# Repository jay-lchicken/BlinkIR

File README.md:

## To the previous review
"Hey! Cool project, but it needs to be polished a bit before it can be approved, you can organise the files in speicific folders such as PCB/etc. I also believe this can be cost optimized a lot, please take a look at the docs, right now you can get 54$ worth of grant for the project but your BOM is totalling to 3 times of that, you should save costs on the PCBA, by trying to fit all components on one side, using components only from standard libray, getting only 2 pcba rather than 5, etc."

I will reorganise the files into the folders. However, for the cost optimisation, it is not really possible for this project since the LEDs cannot be on the same side as the phototransistor and thus require a double-sided assembly. Getting only 2pcba rather than 5 only saves $10, so I may as well go with 5. I can pay the extra price that the grant cannot cover. also, some components are really big and cannot be on the same side as phototransistor else it would hit the ground, like the 47uf electrolytic capacitor

### The sample code in the repository basically lights up the corresponding LEDs when the phototransistor detects black. The code also uses button 1 to start the program
# Introduction

I created this project when I saw a super fast line tracing robot. I thought about what was needed and since one of the most crucial components for a line tracing robot is the IR Array Sensor, I decided

What if I can make one of the most responsive and feature-packed IR Sensor ever made.

# Description

I took inspiration from the Pololu QTR-8A. It is equipped with 8 IR emitters and 8 IR Recievers (or maybe phototransistors, I'm not sure).

I did the same and put it into my PCB with 8 IR emitters and 8 phototransistors that uses the voltage divider rule to give users the reading.

Doing this, I realised that the project ended up being just a normal IR Array sensor. I thought hard about how I could make it unique. Personally, I have building robots since young and it came to my mind
that if I can solve all the problems I previously had with a robot by implementing the solution in the PCB, it would be great! 

I usually hate using the Serial Monitor when debugging my hardware code, so I decided to add 8 SK6812 Neopixel indicator lights to the pcb, one for each IR Sensor but on the other side of the PCB.
The user can have full control of the LEDs but for me, I want to be able to change the light depending on what the phototransistor detects. This helps make debugging with the IR array sensor a lot easier.
When testing line tracking, I can also easily see how I can fine tune the robot when line tracking by looking at the LEDs which I can program to light up when it detects a certain black that meets the treshold value

Competitive robots require a Start/Stop button which I normally use jumper wires to implement. However, these wires often get loose and prevent the robot from starting. Since I am already desiging a PCB, I might as well put some buttons

# How it all fits together
I added a Buck-Boost converter which allow you to put 3.3V to 12V into the IR array sensor. Then, the converter will convert it to 5V which is the proper operating voltage for the circuit.
There are 8 pins which the users can tap into individually with their microcontroller to read the phototransistor readings. There are also another 3 pins. Two for the two INPUT_PULLUP Buttons as well as one for contorlling the daisy chained SK6812 Neopixel LEDs.
Lastly, there are another 3 pins for Vin, GND and turning on the IR Emitter

I decided to go with 4.7K resistors for the phototransistors, this helps balance between the noise and speed for the IR Array Sensor
# Some Schematic Images

# BOM 

## 🧾 Components

| Part Number | Selected By | Qty | Cost |
|------------|------------|-----|------|
| FRC1206F4700TS | System | 15 | $0.08 |
| 0402WGF3300TCE | System | 20 | $0.02 |
| CL10A106KP8NNNC | System | 40 | $0.36 |
| 0603WAF1003T5E | System | 40 | $0.03 |
| NTD3528I7 | System | 44 | $1.66 |
| TPS63070RNMT | System | 5 | $8.42 |
| CL31A226KAHNNNE | System | 14 | $2.50 |
| 0805W8F4702T5E | System | 20 | $0.04 |
| 0805W8F5233T5E | System | 20 | $0.05 |
| KT-0603W | System | 20 | $0.24 |
| RVT102470M0505 | Customer | 20 | $0.58 |
| SK6812 | System | 42 | $3.73 |
| 0805W8F4701T5E | System | 46 | $0.10 |
| 2.54-1×3P# | Customer | 12 | $0.29 |
| MPT0603GT | System | 44 | $1.83 |
| CL05B104K05NNNC | System | 40 | $0.05 |
| 1206W4F1002T5E | System | 15 | $0.09 |
| CMI060808U22RK7 | System | 20 | $0.34 |
| JSM2302 | Customer | 15 | $0.30 |
| CL10A105KB8NNNC | System | 20 | $0.22 |
| KMR221GLFS | System | 10 | $5.31 |
| 0603WAF470J5E | System | 40 | $0.08 |

## 💰 Cost Summary

| Category | Amount |
|----------|--------|
| Merchandise Total (incl. assembly) | $153.07 |
| Shipping (Estimated) | $8.85 |
| **Subtotal** | **$161.92** |

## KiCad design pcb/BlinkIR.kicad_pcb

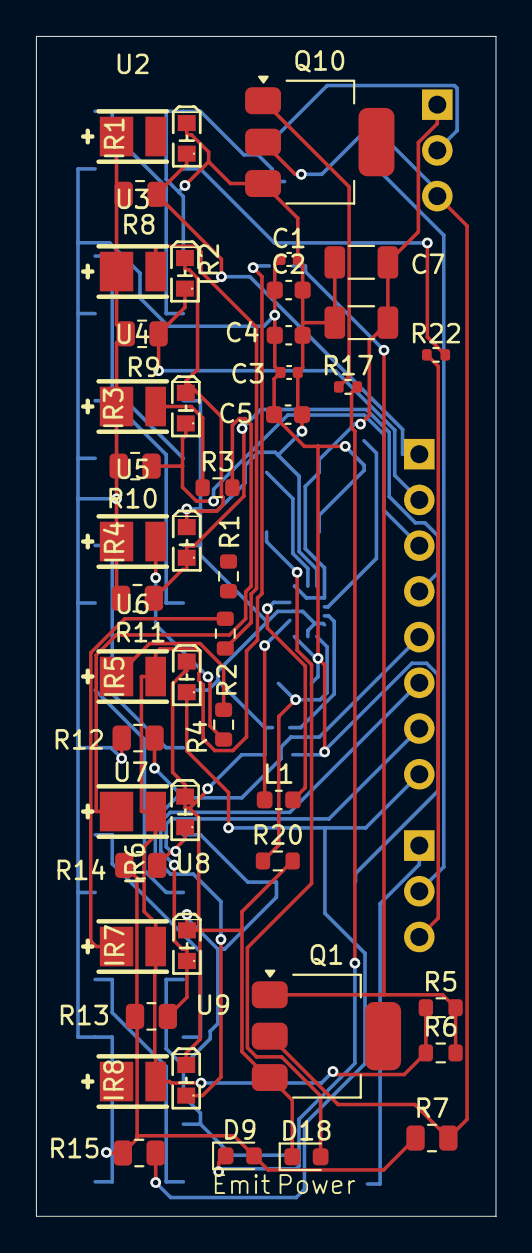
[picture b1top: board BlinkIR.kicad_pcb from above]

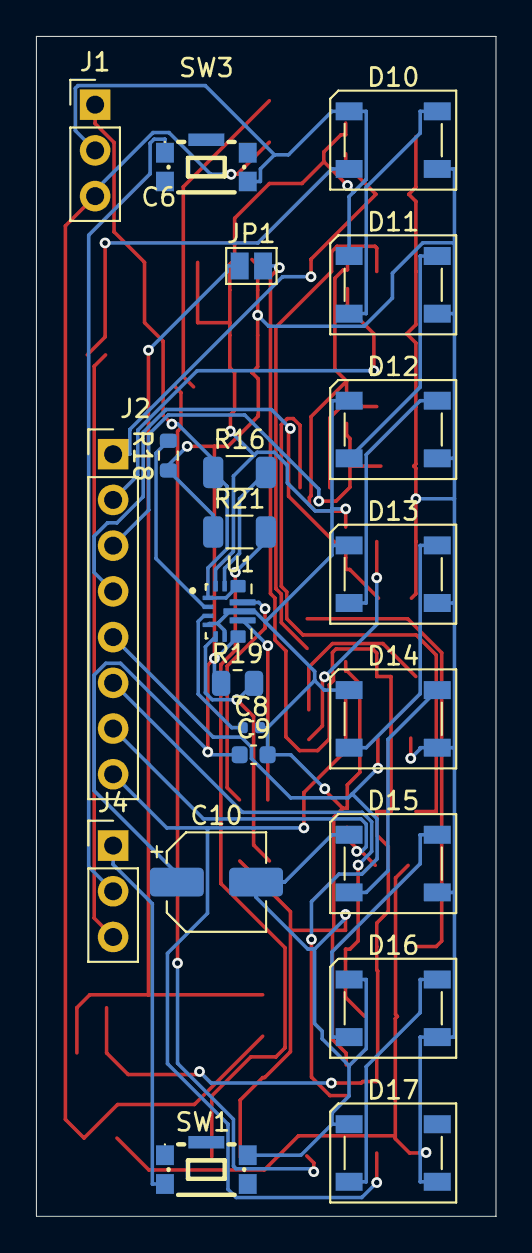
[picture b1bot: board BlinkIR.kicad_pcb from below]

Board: 2 copper layers, 25.5 x 65.6 mm, 68 parts (22 on the bottom side), 42 nets.

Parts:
C1, C3: 0.1uF; C_0402_1005Metric
C2, C4: 1.0uF; C_0603_1608Metric
C5, C9: 10uF; C_0603_1608Metric
C6, C7: 22uF; C_1206_3216Metric
C8: 100nF; C_0402_1005Metric
C10: 47uF; CP_Elec_5x5.4
D9, D18: LED; LED_0603_1608Metric
D10, D11, D12, D13, D14, D15, D16, D17: SK6812; LED_SK6812_PLCC4_5.0x5.0mm_P3.2mm
IR1, IR2, IR3, IR4, IR5, IR6, IR7, IR8: MPT60363T; OPTO-SMD_L1.7-W0.8
J1, J4: Conn_01x03_Pin; PinHeader_1x03_P2.54mm_Vertical
J2: Conn_01x08_Pin; PinHeader_1x08_P2.54mm_Vertical
JP1: SolderJumper_2_Open; SolderJumper-2_P1.3mm_Open_Pad1.0x1.5mm
L1: 2.2uH; L_0603_1608Metric
Q1, Q10: NMOS; SOT-223
R1, R2, R3, R4, R5, R6: 47; R_0603_1608Metric
R7: 47k; R_0805_2012Metric
R8, R9, R10, R11, R12, R13, R14, R15: 4.7k; R_0805_2012Metric
R16: 10k; R_1206_3216Metric
R17, R22: 330; R_0402_1005Metric
R18, R20: 100k; R_0603_1608Metric
R19: 523k; R_0805_2012Metric
R21: 470; R_1206_3216Metric
SW1, SW3: KMR221GLFS; KEY-SMD_KMR2XXGXXX
U1: TPS63070RNMT; VREG_TPS63070RNMT
U2, U3, U4, U5, U6, U7, U8, U9: NTD3528I7; LED-SMD_L3.5-W2.8-FD-1

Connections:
/IR1: IR1.1 (C), J2.1, R8.2
/IR2: IR2.1 (C), J2.2, R9.2
/IR3: IR3.1 (C), J2.3, R10.2
/IR4: IR4.1 (C), J2.4, R11.2
/IR5: IR8.1 (C), J2.5, R12.2
/IR6: IR7.1 (C), J2.6, R13.2
/IR7: IR6.1 (C), J2.7, R14.2
/IR8: IR5.1 (C), J2.8, R15.2
/IR_ON: J1.3, Q1.2 (G), Q10.2 (G), R7.2
GND: C1.2, C2.2, C3.2, C4.2, C5.2, C6.1, C7.1, C8.2, C9.2, C10.2, D10.1 (VSS), D11.1 (VSS), D12.1 (VSS), D13.1 (VSS), D14.1 (VSS), D15.1 (VSS), D16.1 (VSS), D17.1 (VSS), D18.1 (K), IR1.2 (E), IR2.2 (E), IR3.2 (E), IR4.2 (E), IR5.2 (E), IR6.2 (E), IR7.2 (E), IR8.2 (E), J1.2, Q1.3 (S), Q10.3 (S), R20.2, SW1.2, SW3.4, U1.4 (GND), U1.6 (FB2), U1.10 (PGND), U1.15 (VSEL)
unnamed: D9.1 (K), R17.2
unnamed: D10.2 (DIN), R22.2
unnamed: D10.4 (DOUT), D11.2 (DIN)
unnamed: D11.4 (DOUT), D12.2 (DIN)
unnamed: D12.4 (DOUT), D13.2 (DIN)
unnamed: D13.4 (DOUT), D14.2 (DIN)
unnamed: D14.4 (DOUT), D15.2 (DIN)
unnamed: D15.4 (DOUT), D16.2 (DIN)
unnamed: D16.4 (DOUT), D17.2 (DIN)
unnamed: D18.2 (A), R21.2
unnamed: J4.1, SW1.3
unnamed: J4.2, SW3.1
unnamed: J4.3, R22.1
unnamed: JP1.1 (A), Q1.1 (D), R5.2, R6.2
unnamed: JP1.2 (B), R5.1, R6.1, U6.2, U7.2, U8.2, U9.2
unnamed: Q10.1 (D), R17.1
unnamed: R1.1, U2.2
unnamed: R1.2, U9.1
unnamed: R2.1, U3.2
unnamed: R2.2, U8.1
unnamed: R3.1, U4.2
unnamed: R3.2, U7.1
unnamed: R4.1, U5.2
unnamed: R4.2, U6.1
unnamed: R16.2, U1.14 (EN)
unnamed: R19.2, R20.1, U1.5 (FB)
unnamed: L1.2, U1.11 (L1)
unnamed: L1.1, U1.9 (L2)
unnamed: R18.2, U1.2 (PG)
unnamed: C8.1, U1.3 (VAUX)
VCC: C1.1, C2.1, C3.1, C4.1, C5.1, C9.1, C10.1, D9.2 (A), D10.3 (VDD), D11.3 (VDD), D12.3 (VDD), D13.3 (VDD), D14.3 (VDD), D15.3 (VDD), D16.3 (VDD), D17.3 (VDD), R7.1, R8.1, R9.1, R10.1, R11.1, R12.1, R13.1, R14.1, R15.1, R18.1, R19.1, R21.1, U1.7_8 (VOUT), U2.1, U3.1, U4.1, U5.1
Vin: C6.2, C7.2, J1.1, R16.1, U1.1 (PS/SYNC), U1.12_13 (VIN)

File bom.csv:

Designator,Footprint,Quantity,Value,LCSC Part #
"C1, C3",0402,2,0.1uF,
C10,CP_Elec_5x5.4,1,47uF,
"C2, C4",0603,2,1.0uF,
"C5, C9",0603,2,10uF,
"C6, C7",1206,2,22uF,
C8,0402,1,100nF,
"D10, D11, D12, D13, D14, D15, D16, D17",LED_SK6812_PLCC4_5.0x5.0mm_P3.2mm,8,SK6812,
"D18, D9",0603,2,LED,
"IR1, IR2, IR3, IR4, IR5, IR6, IR7, IR8",OPTO-SMD_L1.7-W0.8,8,MPT60363T,C50493
"J1, J4",PinHeader_1x03_P2.54mm_Vertical,2,Conn_01x03_Pin,
J2,PinHeader_1x08_P2.54mm_Vertical,1,Conn_01x08_Pin,
L1,0603,1,2.2uH,
"Q1, Q10",SOT-223,2,NMOS,
"R1, R2, R3, R4, R5, R6",0603,6,47,
"R10, R11, R12, R13, R14, R15, R8, R9",0805,8,4.7k,
R16,1206,1,10k,
"R17, R22",0402,2,330,
"R18, R20",0603,2,100k,
R19,0805,1,523k,
R21,1206,1,470,
R7,0805,1,47k,
"SW1, SW3",KEY-SMD_KMR2XXGXXX,2,KMR221GLFS,C72443
U1,VREG_TPS63070RNMT,1,TPS63070RNMT,
"U2, U3, U4, U5, U6, U7, U8, U9",LED-SMD_L3.5-W2.8-FD-1,8,NTD3528I7,C7464751

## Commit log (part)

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2026-06-16 reorganised
